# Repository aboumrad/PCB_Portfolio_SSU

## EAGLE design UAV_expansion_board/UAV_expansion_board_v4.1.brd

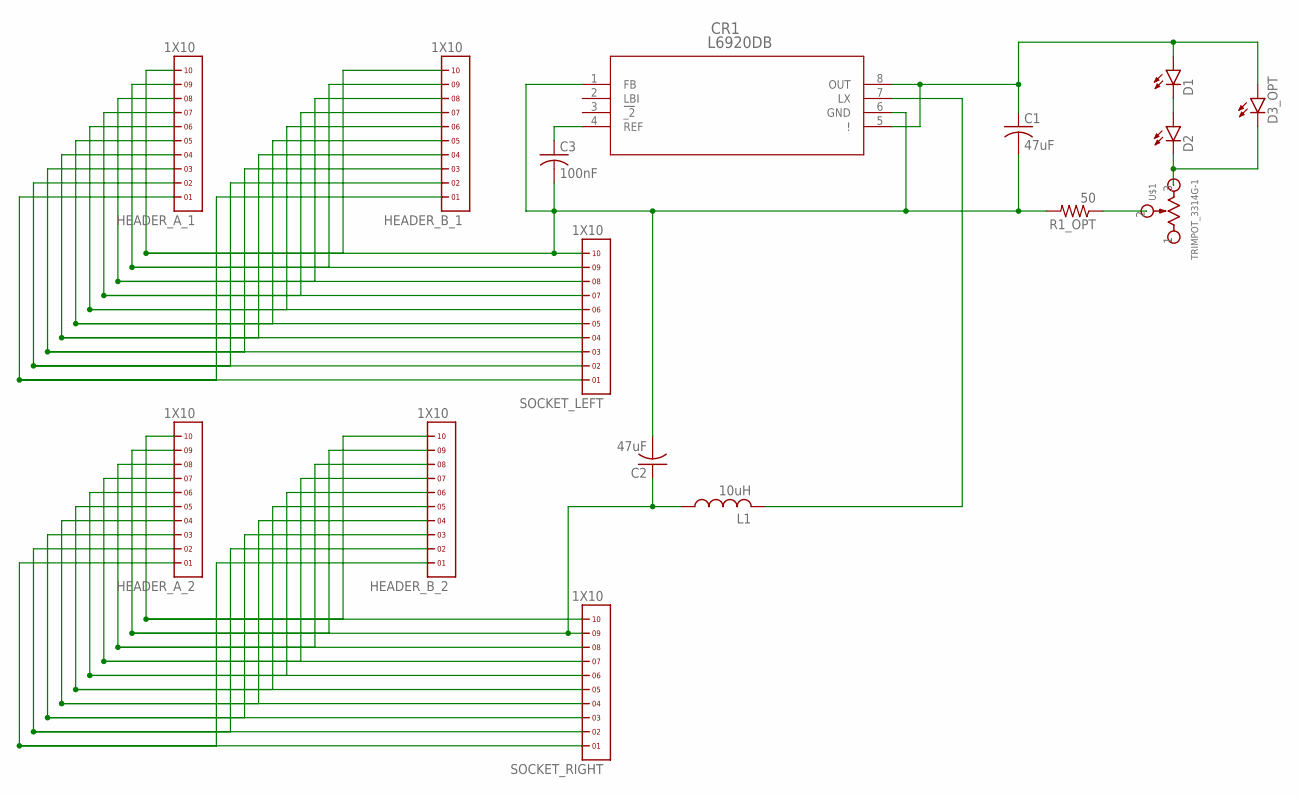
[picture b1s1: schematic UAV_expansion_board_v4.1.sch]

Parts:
C1, C2: 47uF; C1206
C3: 100nF; C1206
CR1: L6920DB; MSOP-8
D1, D2, D3_OPT: SFH4243-Q1R2
HEADER_A_1, HEADER_A_2: 1X10
HEADER_B_1, HEADER_B_2: 1X10
L1: 10uH; R1210
R1_OPT: 50; R0805
SOCKET_LEFT: 1X10
SOCKET_RIGHT: 1X10
U$1: TRIMPOT_3314G-1; 3314G-1

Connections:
unnamed: HEADER_A_1.1, HEADER_B_1.1, SOCKET_LEFT.1
unnamed: HEADER_A_1.2, HEADER_B_1.2, SOCKET_LEFT.2
unnamed: HEADER_A_1.3, HEADER_B_1.3, SOCKET_LEFT.3
unnamed: HEADER_A_1.5, HEADER_B_1.5, SOCKET_LEFT.5
unnamed: HEADER_A_1.4, HEADER_B_1.4, SOCKET_LEFT.4
unnamed: HEADER_A_2.1, HEADER_B_2.1, SOCKET_RIGHT.1
unnamed: HEADER_A_1.6, HEADER_B_1.6, SOCKET_LEFT.6
unnamed: HEADER_A_2.2, HEADER_B_2.2, SOCKET_RIGHT.2
unnamed: HEADER_A_2.3, HEADER_B_2.3, SOCKET_RIGHT.3
unnamed: HEADER_A_1.7, HEADER_B_1.7, SOCKET_LEFT.7
unnamed: HEADER_A_2.4, HEADER_B_2.4, SOCKET_RIGHT.4
unnamed: HEADER_A_2.5, HEADER_B_2.5, SOCKET_RIGHT.5
unnamed: HEADER_A_1.8, HEADER_B_1.8, SOCKET_LEFT.8
unnamed: HEADER_A_2.6, HEADER_B_2.6, SOCKET_RIGHT.6
unnamed: HEADER_A_2.7, HEADER_B_2.7, SOCKET_RIGHT.7
unnamed: HEADER_A_1.9, HEADER_B_1.9, SOCKET_LEFT.9
unnamed: HEADER_A_2.8, HEADER_B_2.8, SOCKET_RIGHT.8
unnamed: C2.1, HEADER_A_2.9, HEADER_B_2.9, L1.1, SOCKET_RIGHT.9
unnamed: C1.2, C2.2, C3.2, CR1.1 (FB), CR1.6 (GND), HEADER_A_1.10, HEADER_B_1.10, R1_OPT.2, SOCKET_LEFT.10
unnamed: HEADER_A_2.10, HEADER_B_2.10, SOCKET_RIGHT.10
unnamed: C3.1, CR1.4 (REF)
unnamed: C1.1, CR1.5 (!), CR1.8 (OUT), D1.A, D3_OPT.A
unnamed: CR1.7 (LX), L1.2
unnamed: D1.K (C), D2.A
unnamed: D2.K (C), D3_OPT.K (C), U$1.3
unnamed: R1_OPT.1, U$1.2

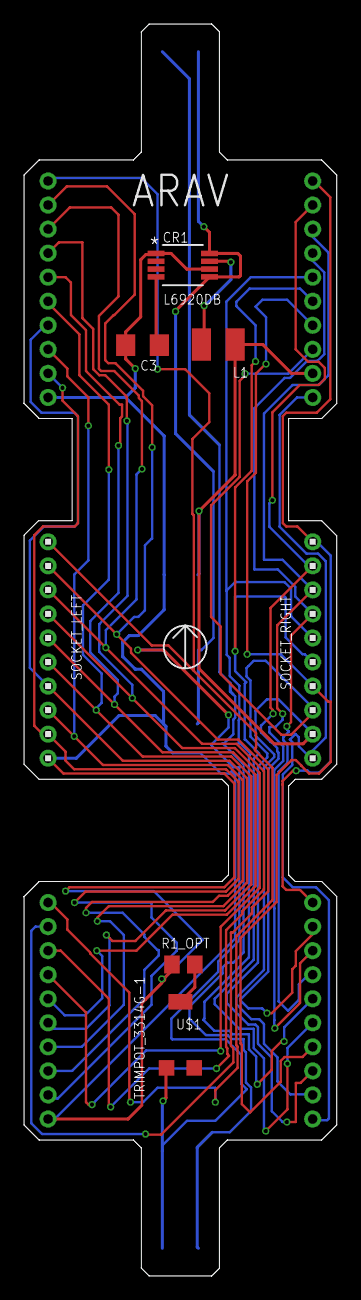
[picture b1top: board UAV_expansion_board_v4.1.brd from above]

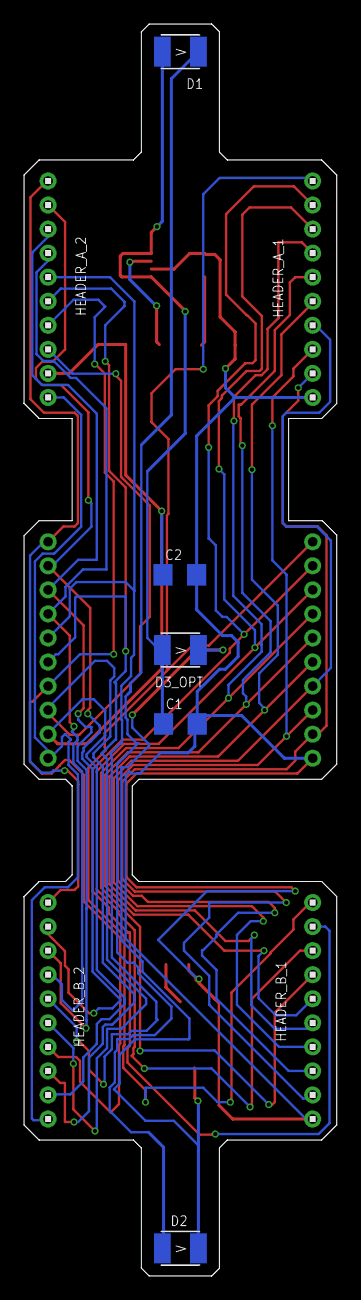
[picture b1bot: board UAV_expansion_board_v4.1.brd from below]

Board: 2 copper layers, 26.0 x 104.1 mm, 16 parts (9 on the bottom side), 26 nets.

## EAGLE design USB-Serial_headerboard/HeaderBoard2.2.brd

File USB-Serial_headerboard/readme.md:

USB-Serial headerboard, creating while working at SSU E/PO

    1. Modified schematic from former supervisor to resolve brownouts
    2. Handtraced PCB layout
    3. Image of PCB layout
    4. Image of populated board,

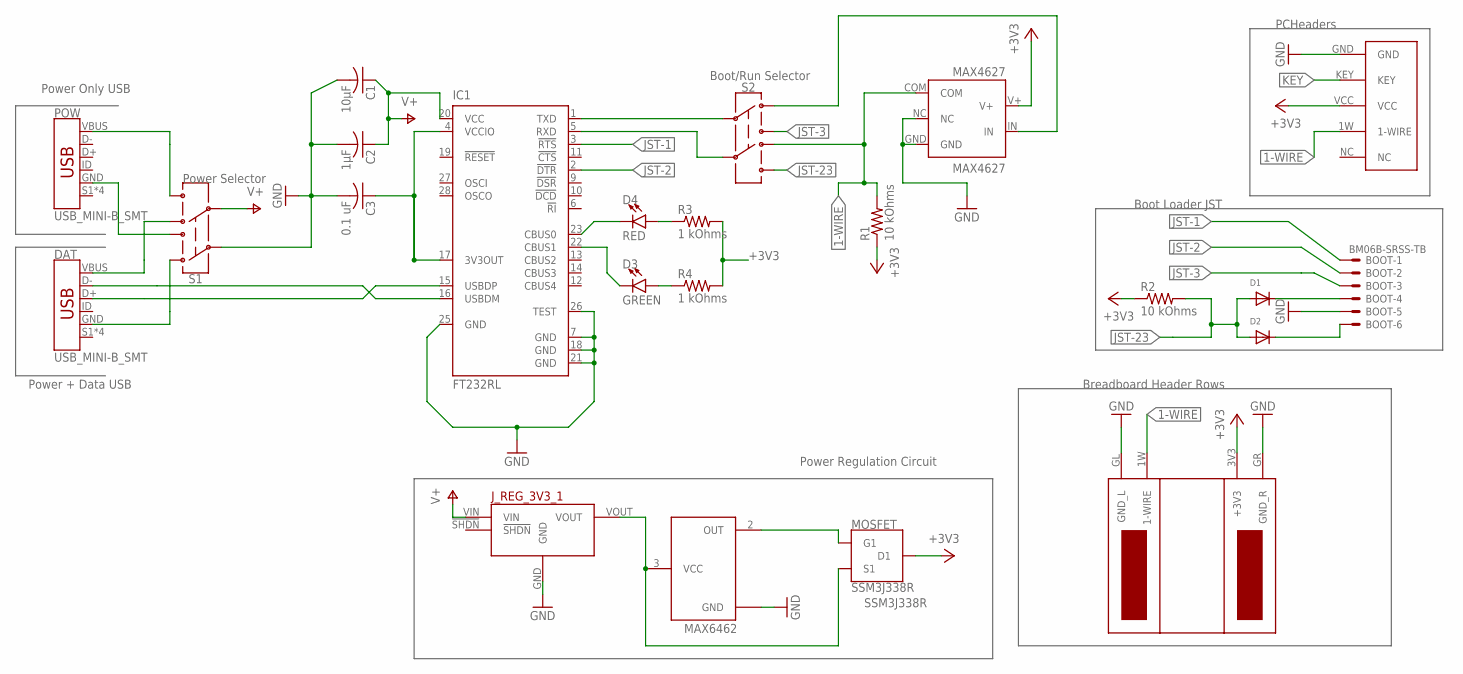
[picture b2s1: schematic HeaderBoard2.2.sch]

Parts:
BOOT: BM06B-SRSS-TB
C1: 10µF; C0805
C2: 1µF; C0805
C3: 0.1 uF; C0805
D1, D2: DIODESOD-123; SOD-123
D3: GREEN; LED-0603
D4: RED; LED-0603
DAT: USB_MINI-B_SMT; USB-MINIB
IC1: FT232RL; SSOP28
J_REG_3V3_1: 3V3_VOLTAGE_REGULATOR
MAX4627: MAX4627
MAX6462: MAX6461; SC70-3L
MOSFET: SSM3J338R; SOT23
POW: USB_MINI-B_SMT; USB-MINIB
R1, R2: 10 kOhms; R0603
R3, R4: 1 kOhms; R0603
S1, S2: SWITCH-DPDT-SMD-AYZ0202; SWITCH_DPDT_SMD_AYZ0202
U$3: BBHEADERPINS_5R
U$4: PCBOARD_PINS

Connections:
1-WIRE: MAX4627.COM, R1.2, S2.4, U$3.1W (1-WIRE), U$4.1W (1-WIRE)
+3V3: MAX4627.V+, MOSFET.D (D1), R1.1, R2.1, R3.2, R4.2, U$3.3V3 (+3V3), U$4.VCC
GND: BOOT.5, C1.2, C2.2, C3.2, IC1.7 (GND), IC1.18 (GND), IC1.21 (GND), IC1.25 (GND), IC1.26 (TEST), J_REG_3V3_1.GND, MAX4627.GND, MAX4627.NC, MAX6462.1 (GND), S1.2, U$3.GL (GND_L), U$3.GR (GND_R), U$4.GND
JST-1: BOOT.1, IC1.3 (!RTS)
JST-2: BOOT.2, IC1.2 (!DTR)
JST-3: BOOT.3, S2.3
JST-23: D1.A, D2.A, R2.2, S2.6
KEY: U$4.KEY
unnamed: D3.C, IC1.22 (CBUS1)
unnamed: IC1.1 (TXD), S2.2
unnamed: IC1.5 (RXD), S2.5
unnamed: BOOT.6, D2.C
unnamed: DAT.VBUS, S1.4
unnamed: DAT.GND, S1.1
unnamed: POW.GND, S1.3
unnamed: POW.VBUS, S1.6
unnamed: BOOT.4, D1.C
unnamed: MAX4627.IN, S2.1
unnamed: J_REG_3V3_1.VOUT, MAX6462.3 (VCC), MOSFET.S (S1)
unnamed: MAX6462.2 (OUT), MOSFET.G (G1)
unnamed: DAT.D+, IC1.15 (USBDP)
unnamed: DAT.D-, IC1.16 (USBDM)
unnamed: C3.1, IC1.4 (VCCIO), IC1.17 (3V3OUT)
unnamed: D3.A, R4.1
unnamed: D4.A, R3.1
unnamed: D4.C, IC1.23 (CBUS0)
V+: C1.1, C2.1, IC1.20 (VCC), J_REG_3V3_1.VIN, S1.5

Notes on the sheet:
PCHeaders
Boot Loader JST
Power Only USB
Power + Data USB
Power Regulation Circuit
Power Selector
Boot/Run Selector
MAX6462
SSM3J338R
Breadboard Header Rows

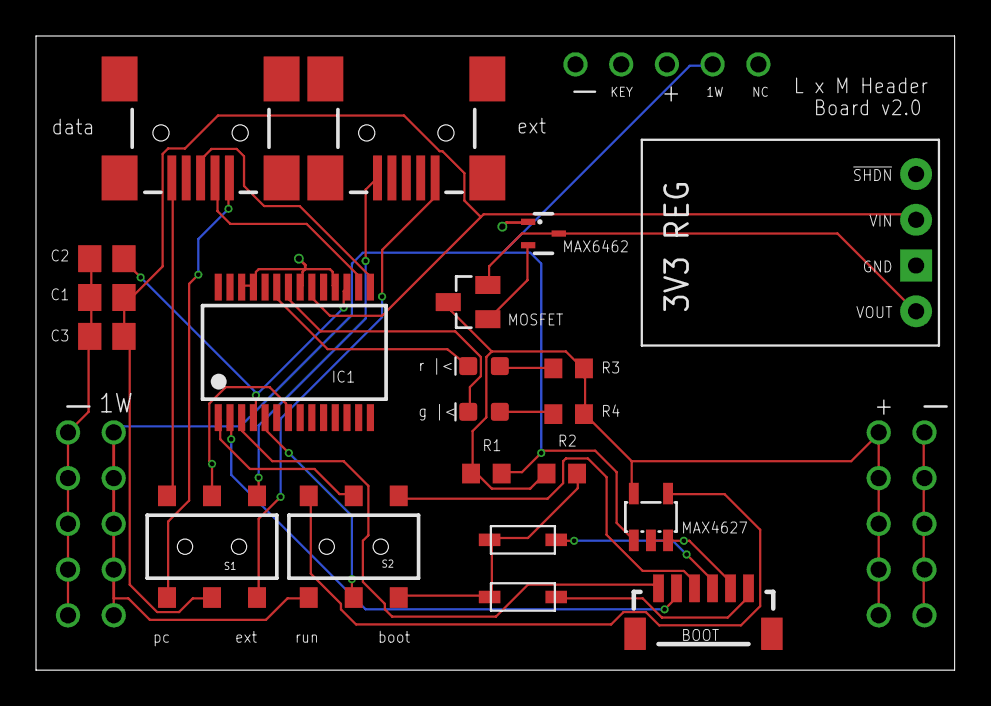
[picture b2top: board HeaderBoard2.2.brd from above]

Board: 4 copper layers, 51.0 x 35.2 mm, 23 parts (0 on the bottom side), 26 nets.

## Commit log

2020-04-14 headerboard layout from E/PO work
2020-04-14 Created readme.md
2020-04-14 moved files to dir
2020-04-14 update image files
2020-04-14 adding files for UAV senior design project

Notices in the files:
parts and their libraries:
SparkFun-LED: Licensing: Creative Commons ShareAlike 4.0 International - https://creativecommons.org/licenses/by-sa/4.0
